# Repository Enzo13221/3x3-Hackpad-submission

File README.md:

# My Keyboard Project

This repository contains the source files for my keyboard firmware. It includes `main.py` for KMK and all necessary supporting files.

---

## Screenshots

### Hackpad
.PNG)
.PNG)

### Schematic

### PCB

### Case
.PNG)
.PNG)
---

## Bill of Materials (BOM)

| Part Name           | Quantity |
|---------------------|----------|
| PCB                 | 1        |
| Cherry MX Switch    | 9        |
| Keycaps             | 9        |
| Seeed XIAO RP2040   | 1        |
| Case                | 1        |
| M3x16 Bolt          | 4        | 
| M3 Heatset          | 4        |
| SK6812 MINI LEDs    | 2        |

---

## Description

This is my 3x3 hackpad key board submission. I had a lot of fun learning how to use Kicad, Fusion, and other software while designing this. It is really simple just the base project plus extra keys and a bigger box. While working on this project I had one thing in mind and that was moving on to more complex projects.

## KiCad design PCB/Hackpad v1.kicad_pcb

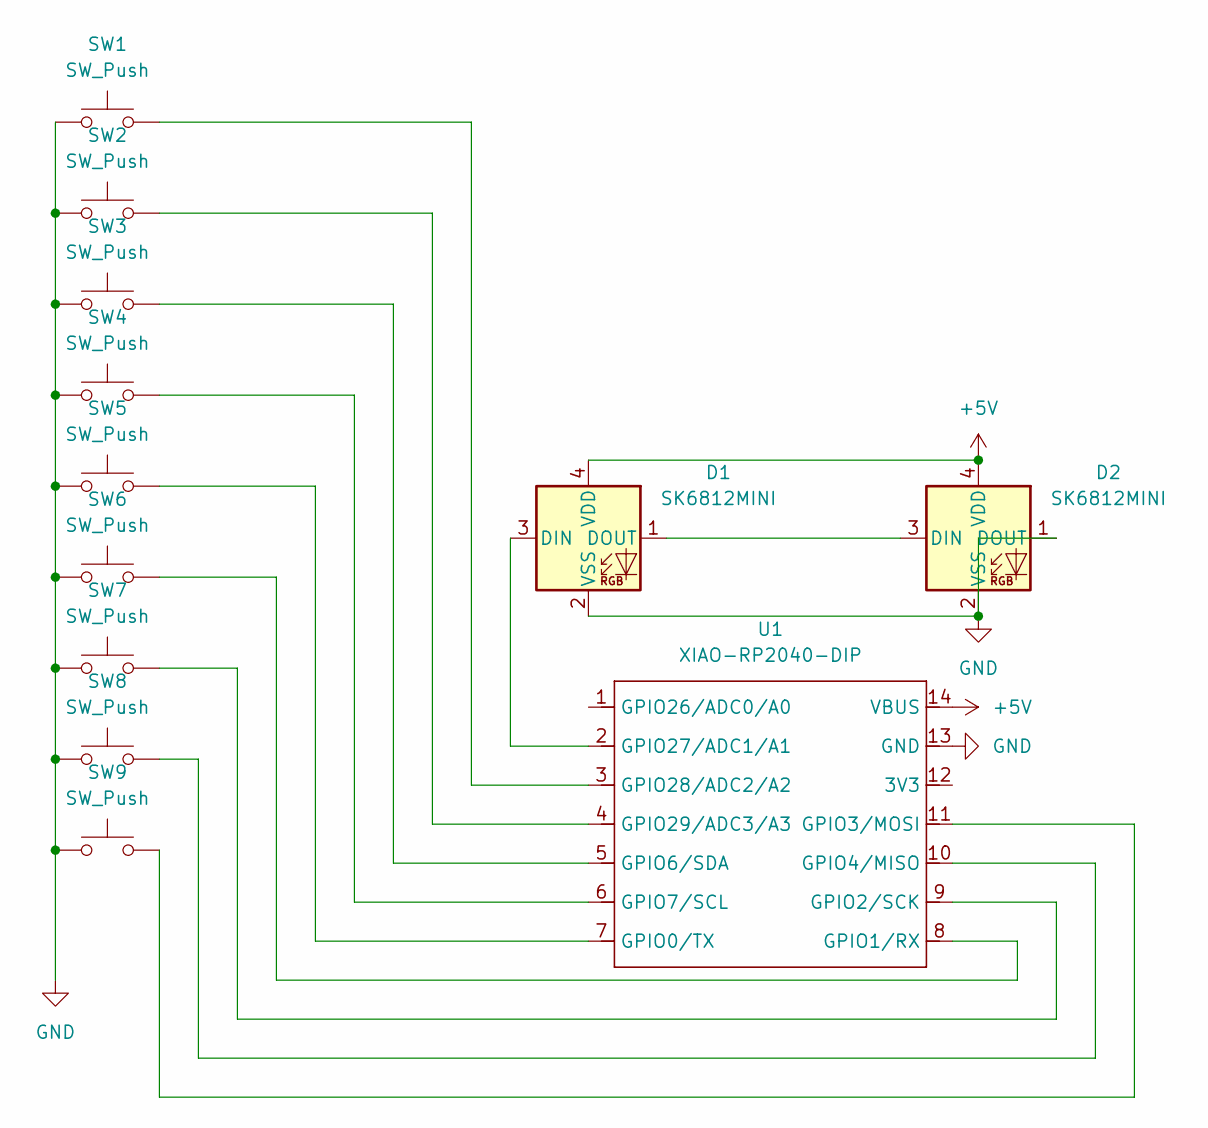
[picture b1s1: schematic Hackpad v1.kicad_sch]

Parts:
D1, D2: SK6812MINI; LED_SK6812MINI_PLCC4_3.5x3.5mm_P1.75mm
SW1, SW2, SW3, SW4, SW5, SW6, SW7, SW8, SW9: SW_Push; SW_Cherry_MX_1.00u_PCB
U1: XIAO-RP2040-DIP

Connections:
+5V: D1.4 (VDD), D2.4 (VDD), U1.14 (VBUS)
GND: D1.2 (VSS), D2.1 (DOUT), D2.2 (VSS), SW1.1, SW2.1, SW3.1, SW4.1, SW5.1, SW6.1, SW7.1, SW8.1, SW9.1, U1.13 (GND)
unnamed: D1.3 (DIN), U1.2 (GPIO27/ADC1/A1)
unnamed: D1.1 (DOUT), D2.3 (DIN)
unnamed: SW5.2, U1.7 (GPIO0/TX)
unnamed: SW6.2, U1.8 (GPIO1/RX)
unnamed: SW7.2, U1.9 (GPIO2/SCK)
unnamed: SW9.2, U1.11 (GPIO3/MOSI)
unnamed: SW8.2, U1.10 (GPIO4/MISO)
unnamed: SW3.2, U1.5 (GPIO6/SDA)
unnamed: SW4.2, U1.6 (GPIO7/SCL)
unnamed: SW1.2, U1.3 (GPIO28/ADC2/A2)
unnamed: SW2.2, U1.4 (GPIO29/ADC3/A3)

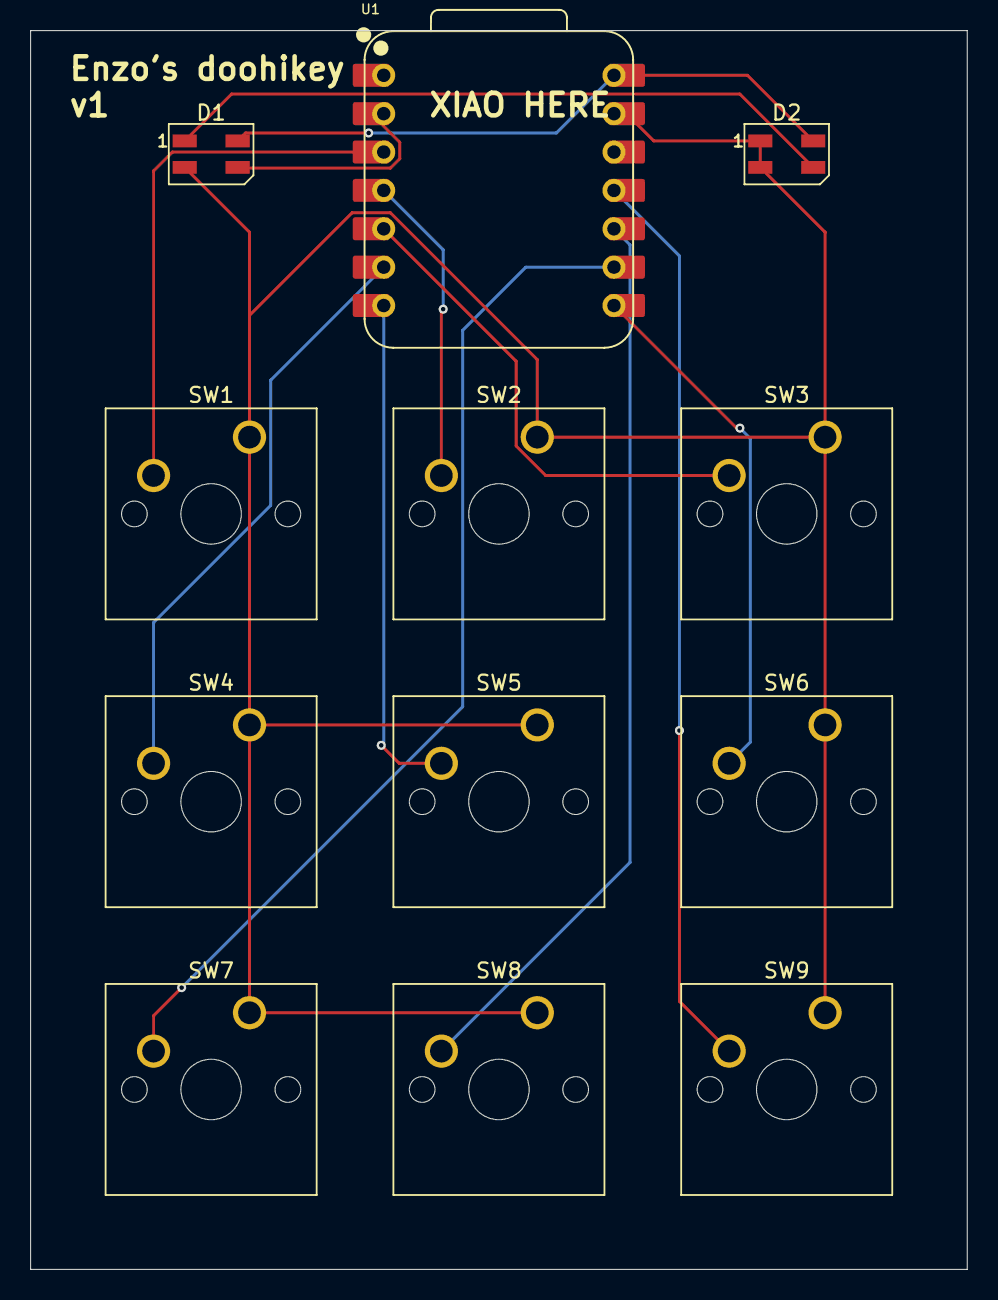
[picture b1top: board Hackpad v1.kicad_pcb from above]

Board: 2 copper layers, 62.0 x 82.0 mm, 12 parts (0 on the bottom side), 13 nets.

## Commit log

2025-12-13 Adding my CAD files
2025-12-13 more CAD
2025-12-16 blank
2025-12-16 README.md
